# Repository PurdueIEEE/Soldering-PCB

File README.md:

# Soldering-PCB
a 4-bit adder used as a soldering practice pcb

Changes to be done for v2
- Update manual

Changes already made in v2 (or decided not to be made)
- ~~Ensure no vias to different signals close to soldering points (i.e. the one by the 9V lines)~~
- ~~Make 9V holes bigger~~
- ~~Consider making resistor pads a tad larger~~
- ~~Consider making 3V linear regulator pads a tad bigger~~ (decided not to)
- ~~Make the resistors values larger and J1 labels.~~
- ~~Consider adding IEEE or Purdue logo on bottom left silkscreen~~
- ~~Make PCB text header larger~~
- ~~Consider making board smaller (see if it will actually save cost)~~ (didn't do this)

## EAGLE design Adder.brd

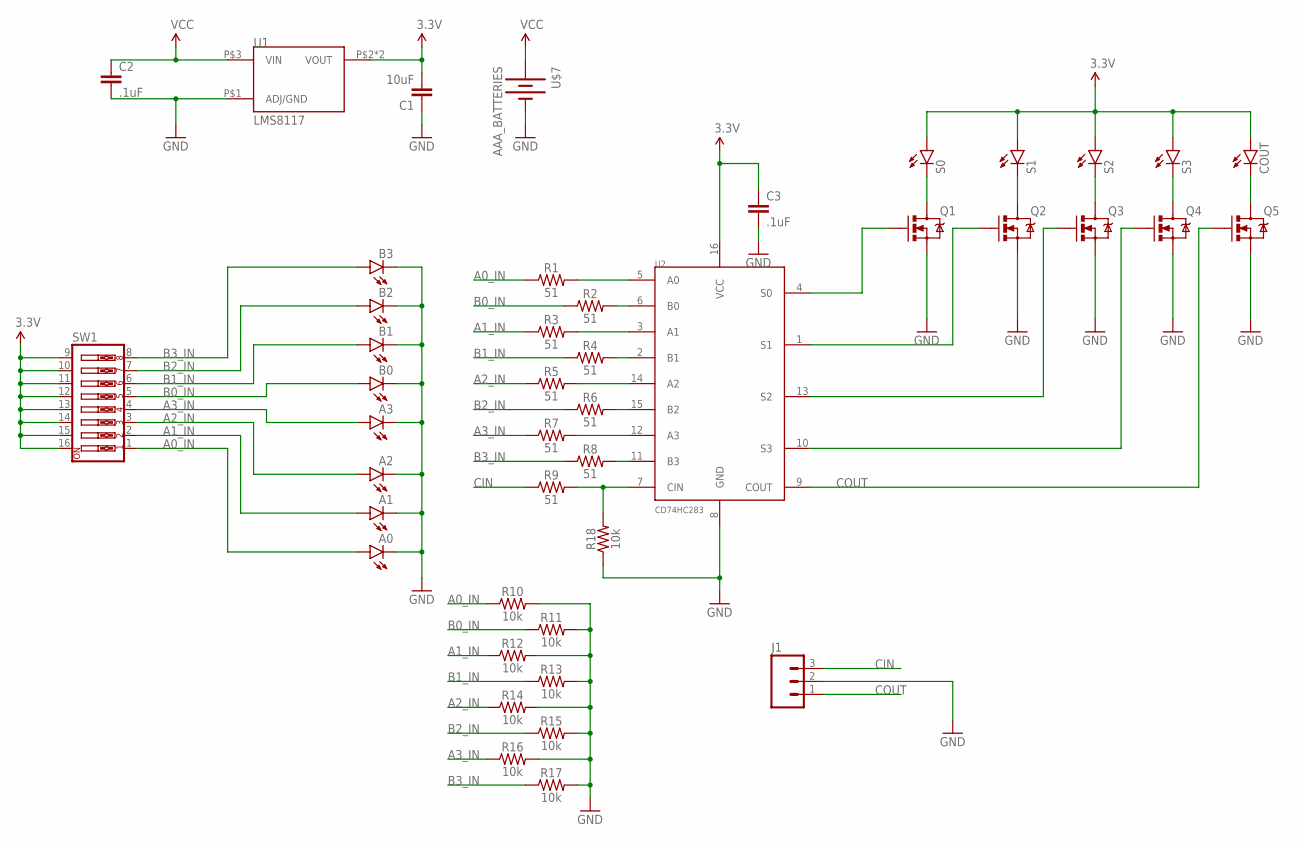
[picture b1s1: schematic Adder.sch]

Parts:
A0, A1, A2, A3: LED5MM
B0, B1, B2, B3: LED5MM
C1: 10uF; 0603-CAP
C2, C3: .1uF; 0603-CAP
COUT: LED5MM
J1: M03PTH; 1X03
Q1, Q2, Q3, Q4, Q5: MOSFET-NCHANNEL2N7000; TO-92
R1, R2, R3, R4, R5, R6, R7, R8, R9: 51; 0805
R10, R11, R12, R13, R14, R15, R16, R17, R18: 10k; 0805
S0, S1, S2, S3: LED5MM
SW1: SW_DIP-8; DIPSWITCH-08
U1: LMS8117; SOT-223
U2: CD74HC283; SO016
U$7: AAA_BATTERIES; WIRE_LEADS

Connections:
3.3V: C1.2, C3.1, COUT.A, S0.A, S1.A, S2.A, S3.A, SW1.9, SW1.10, SW1.11, SW1.12, SW1.13, SW1.14, SW1.15, SW1.16, U1.P$2 (VOUT), U1.P$4 (VOUT), U2.16 (VCC)
A0_IN: A0.A, R1.1, R10.1, SW1.1
A1_IN: A1.A, R3.1, R12.1, SW1.2
A2_IN: A2.A, R5.1, R14.1, SW1.3
A3_IN: A3.A, R7.1, R16.1, SW1.4
B0_IN: B0.A, R2.1, R11.1, SW1.5
B1_IN: B1.A, R4.1, R13.1, SW1.6
B2_IN: B2.A, R6.1, R15.1, SW1.7
B3_IN: B3.A, R8.1, R17.1, SW1.8
CIN: J1.3, R9.1
COUT: J1.1, Q5.2 (G), U2.9 (COUT)
GND: A0.K (C), A1.K (C), A2.K (C), A3.K (C), B0.K (C), B1.K (C), B2.K (C), B3.K (C), C1.1, C2.2, C3.2, J1.2, Q1.1 (S), Q2.1 (S), Q3.1 (S), Q4.1 (S), Q5.1 (S), R10.2, R11.2, R12.2, R13.2, R14.2, R15.2, R16.2, R17.2, R18.1, U1.P$1 (ADJ/GND), U2.8 (GND), U$7.P$1 (-)
unnamed: Q2.2 (G), U2.1 (S1)
unnamed: Q3.2 (G), U2.13 (S2)
unnamed: Q4.2 (G), U2.10 (S3)
unnamed: Q1.2 (G), U2.4 (S0)
unnamed: Q1.3 (D), S0.K (C)
unnamed: Q2.3 (D), S1.K (C)
unnamed: Q3.3 (D), S2.K (C)
unnamed: Q4.3 (D), S3.K (C)
unnamed: COUT.K (C), Q5.3 (D)
unnamed: R1.2, U2.5 (A0)
unnamed: R2.2, U2.6 (B0)
unnamed: R3.2, U2.3 (A1)
unnamed: R4.2, U2.2 (B1)
unnamed: R5.2, U2.14 (A2)
unnamed: R6.2, U2.15 (B2)
unnamed: R7.2, U2.12 (A3)
unnamed: R8.2, U2.11 (B3)
unnamed: R9.2, R18.2, U2.7 (CIN)
VCC: C2.1, U1.P$3 (VIN), U$7.P$2 (+)

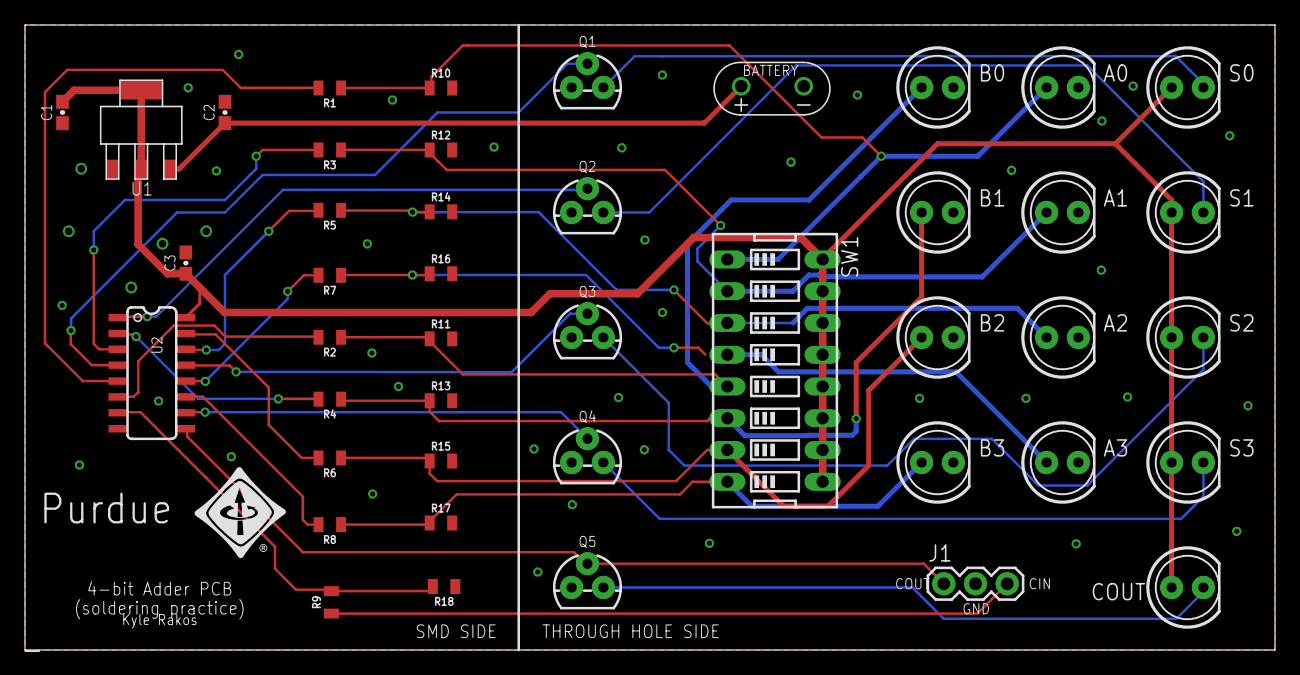
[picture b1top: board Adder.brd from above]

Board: 2 copper layers, 100.0 x 50.0 mm, 44 parts (0 on the bottom side), 31 nets.

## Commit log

2017-07-31 Initital commit
2017-07-31 Updated a few traces
2017-10-23 User Manual in LaTeX
    Datasheet for the binary adder IC was added. Guide for end users
    following proper IEEE branding was written that describes basic
    operation and troubleshooting. The user manual assumes the user has
    completed soldering instruction and work so that the PCB is ready for
    use.
2017-10-23 Added the Figure
    Something in the .gitignore was not allowing the logo to be added.
2017-10-24 Implemented Kyle's Suggestions for the Manual
    Warning given about testing for power-to-ground shorts. Better
    differentiation between battery voltage and DC bus voltage at 3.3 V.
    Certain troubleshooting steps have better descriptions of how rare they
    are.
2017-10-24 Added Pictures of Soldered PCB to Manual
    Manuals has two figures: one of the populated PCB and another showing
    how the LEDs light up during addition.
2017-11-20 Updated readme with notes for future fixes
2018-02-04 Made updates for v2
2018-02-18 Finished updating v2 of board
    Addressed comments in readme and refined layout
2018-02-18 updated readme and quick ERC check
2018-02-19 increased minimum trace width
2021-09-11 Labels for resistor values

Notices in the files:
parts and their libraries:
SparkFun-LED: Licensing: Creative Commons ShareAlike 4.0 International - https://creativecommons.org/licenses/by-sa/4.0
